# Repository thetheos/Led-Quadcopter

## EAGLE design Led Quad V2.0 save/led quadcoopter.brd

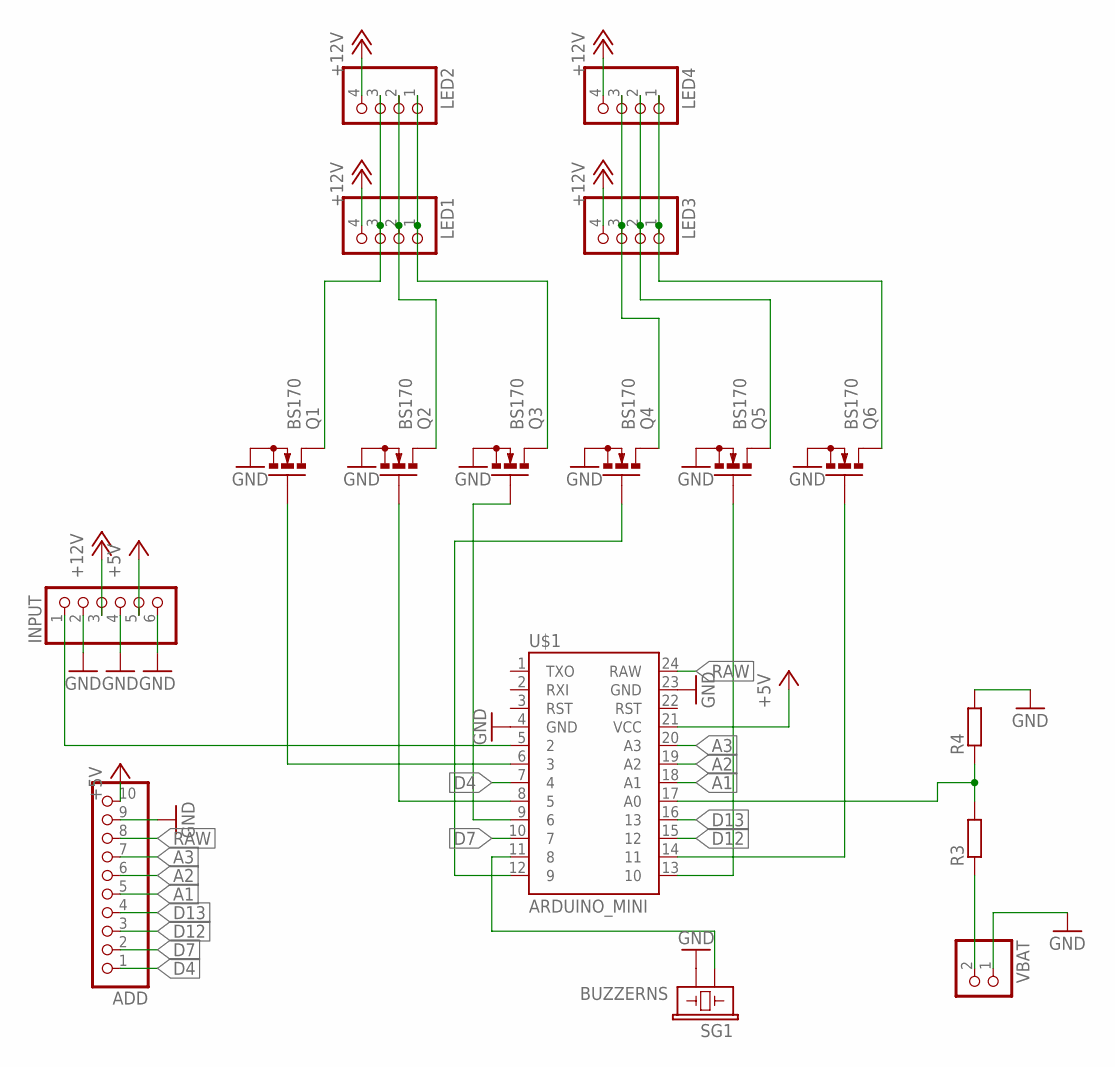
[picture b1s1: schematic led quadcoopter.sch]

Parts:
ADD: PINHD-1X10; 1X10
INPUT: PINHD-1X6; 1X06
LED1, LED2, LED3, LED4: PINHD-1X4; 1X04
Q1, Q2, Q3, Q4, Q5, Q6: BS170; SOT54E
R3, R4: R-EU_0207/10; 0207/10
SG1: BUZZERNS; BUZZER-12MM-NS
U$1: ARDUINO_MINI
VBAT: PINHD-1X2; 1X02

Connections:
+5V: ADD.10, INPUT.5, U$1.21 (VCC)
+12V: INPUT.3, LED1.4, LED2.4, LED3.4, LED4.4
A1: ADD.5, U$1.18 (A1)
A2: ADD.6, U$1.19 (A2)
A3: ADD.7, U$1.20 (A3)
D4: ADD.1, U$1.7 (4)
D7: ADD.2, U$1.10 (7)
D12: ADD.3, U$1.15 (12)
D13: ADD.4, U$1.16 (13)
GND: ADD.9, INPUT.2, INPUT.4, INPUT.6, Q1.S, Q2.S, Q3.S, Q4.S, Q5.S, Q6.S, R4.2, SG1.- (2), U$1.4 (GND), U$1.23 (GND), VBAT.1
unnamed: LED1.3, LED2.3, Q1.D
unnamed: LED1.2, LED2.2, Q2.D
unnamed: SG1.+ (1), U$1.11 (8)
unnamed: INPUT.1, U$1.5 (2)
unnamed: LED1.1, LED2.1, Q3.D
unnamed: LED3.3, LED4.3, Q4.D
unnamed: LED3.2, LED4.2, Q5.D
unnamed: LED3.1, LED4.1, Q6.D
unnamed: Q1.G, U$1.6 (3)
unnamed: Q2.G, U$1.8 (5)
unnamed: Q3.G, U$1.9 (6)
unnamed: Q4.G, U$1.12 (9)
unnamed: Q5.G, U$1.13 (10)
unnamed: Q6.G, U$1.14 (11)
unnamed: R3.1, VBAT.2
unnamed: R3.2, R4.1, U$1.17 (A0)
RAW: ADD.8, U$1.24 (RAW)

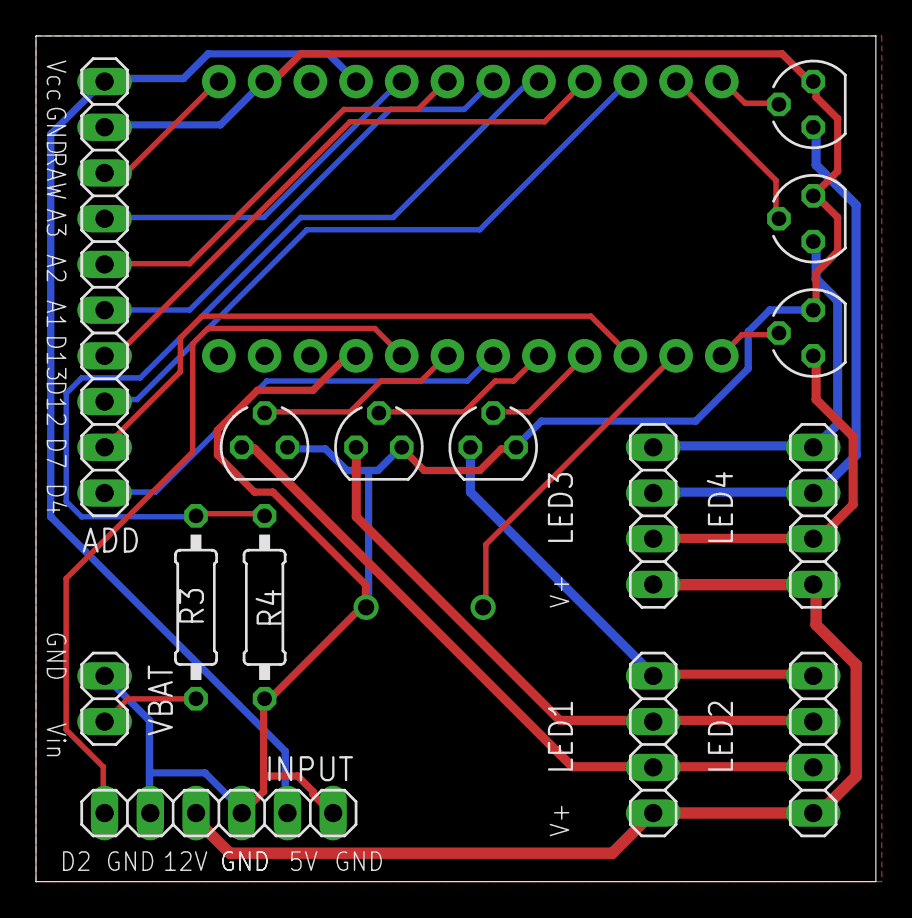
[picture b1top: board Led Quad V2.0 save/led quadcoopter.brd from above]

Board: 2 copper layers, 46.7 x 47.0 mm, 17 parts (1 on the bottom side), 27 nets.

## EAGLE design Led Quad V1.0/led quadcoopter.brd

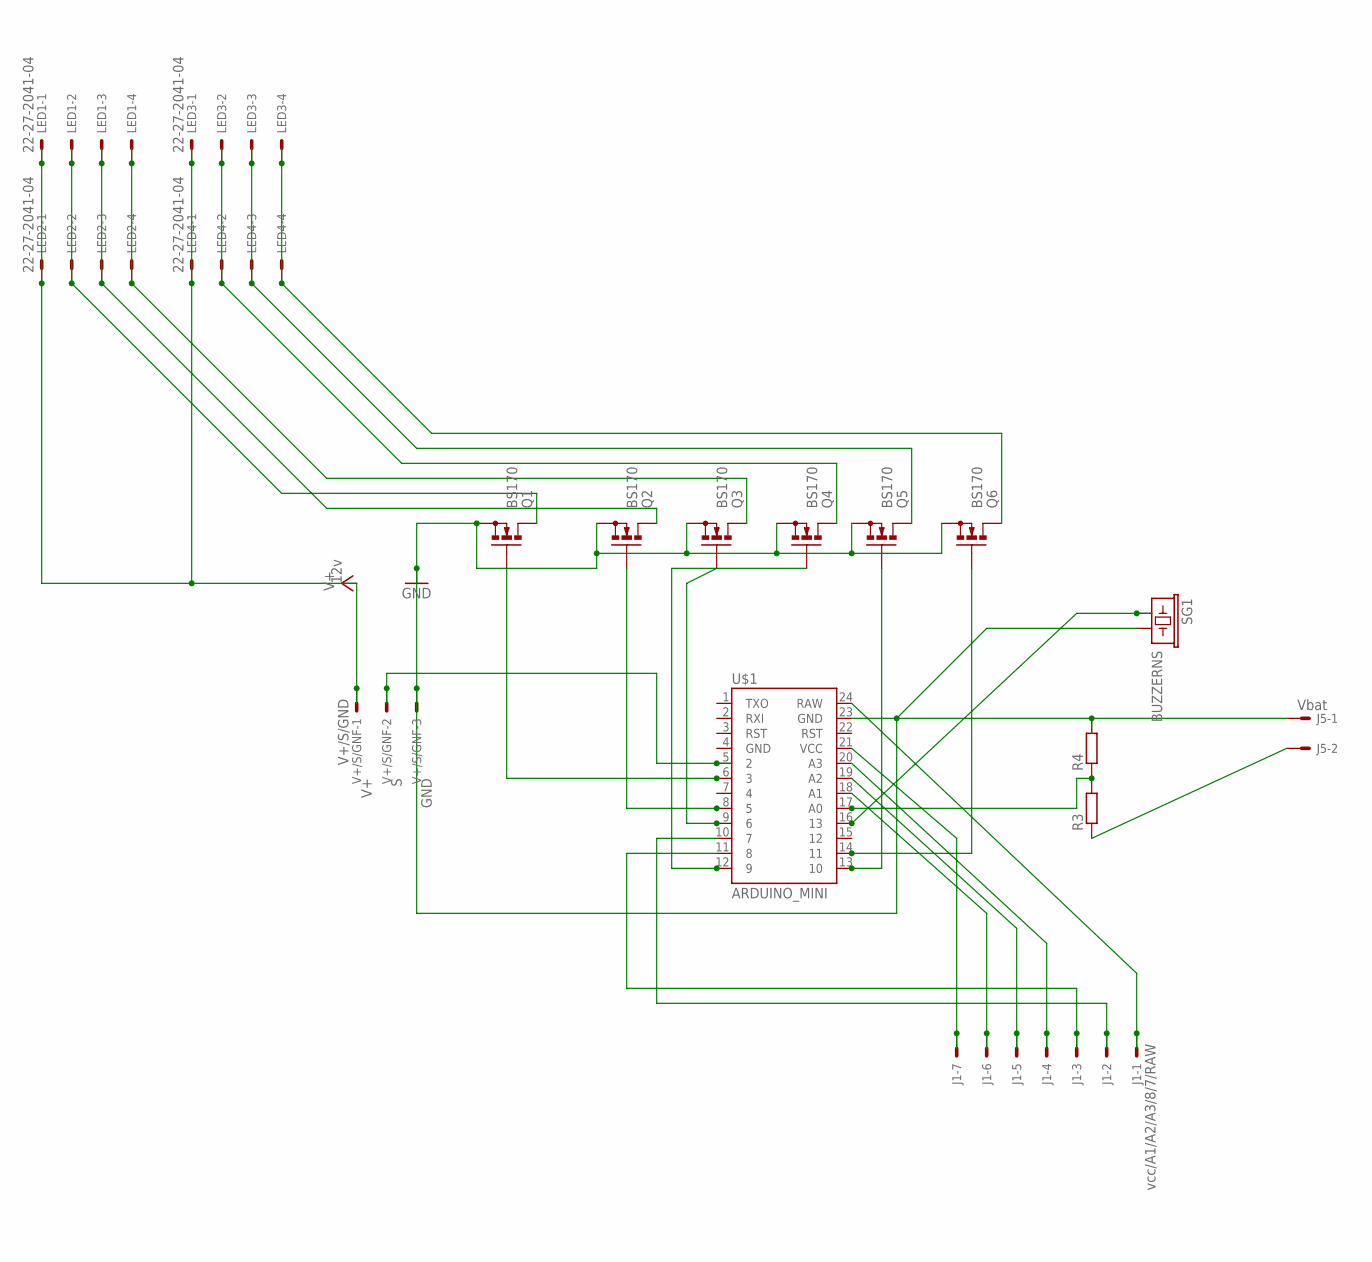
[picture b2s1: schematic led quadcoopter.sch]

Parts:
J1: vcc/A1/A2/A3/8/7/RAW; 6410-07
J5: Vbat; 6410-02
LED1, LED2, LED3, LED4: 22-27-2041-04; 6410-04
Q1, Q2, Q3, Q4, Q5, Q6: BS170; SOT54E
R3, R4: R-EU_0207/10; 0207/10
SG1: BUZZERNS; BUZZER-12MM-NS
U$1: ARDUINO_MINI
V+/S/GNF: V+/S/GND; 6410-03

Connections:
GND: J5.1, Q1.S, Q2.S, Q3.S, Q4.S, Q5.S, Q6.S, R4.2, SG1.- (2), U$1.23 (GND), V+/S/GNF.3
unnamed: LED1.4, LED2.4, Q3.D
unnamed: R3.2, R4.1, U$1.17 (A0)
unnamed: SG1.+ (1), U$1.16 (13)
unnamed: J1.1, U$1.24 (RAW)
unnamed: J1.7, U$1.21 (VCC)
unnamed: J1.6, U$1.18 (A1)
unnamed: J1.5, U$1.19 (A2)
unnamed: LED1.2, LED2.2, Q1.D
unnamed: LED1.3, LED2.3, Q2.D
unnamed: LED3.2, LED4.2, Q4.D
unnamed: LED3.3, LED4.3, Q5.D
unnamed: LED3.4, LED4.4, Q6.D
unnamed: U$1.5 (2), V+/S/GNF.2
unnamed: J1.4, U$1.20 (A3)
unnamed: J1.3, U$1.11 (8)
unnamed: Q1.G, U$1.6 (3)
unnamed: Q2.G, U$1.8 (5)
unnamed: Q3.G, U$1.9 (6)
unnamed: Q4.G, U$1.12 (9)
unnamed: Q5.G, U$1.13 (10)
unnamed: Q6.G, U$1.14 (11)
unnamed: J1.2, U$1.10 (7)
V+: LED1.1, LED2.1, LED3.1, LED4.1, V+/S/GNF.1
VBAT: J5.2, R3.1

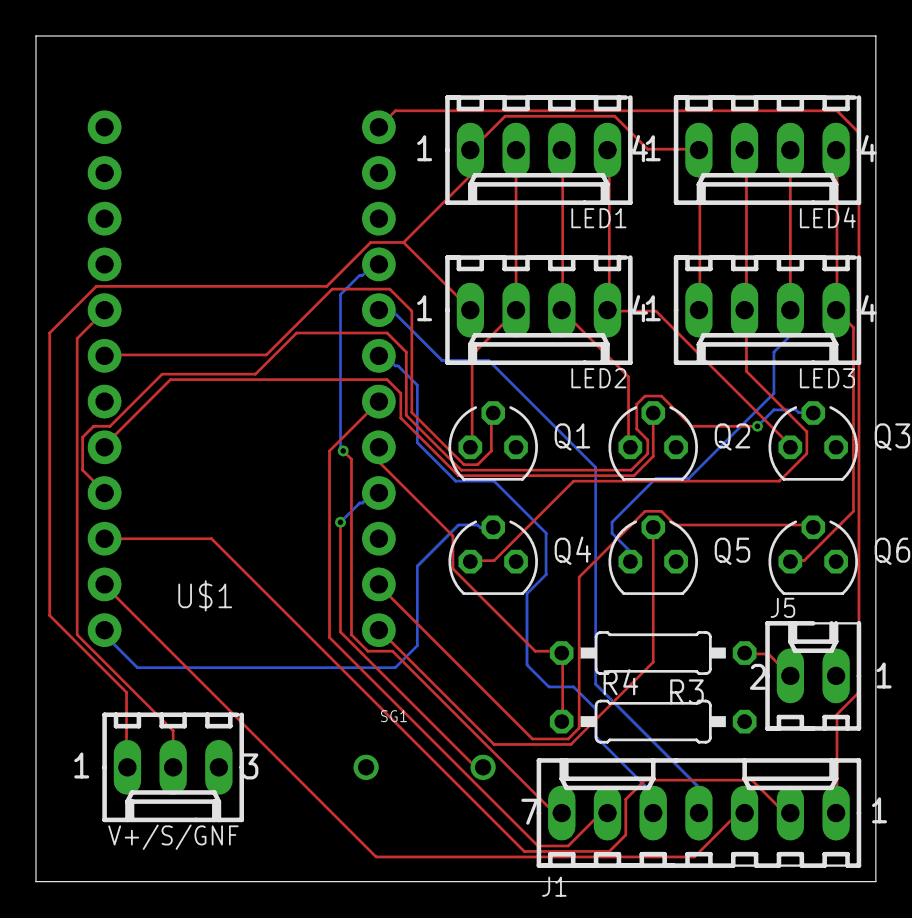
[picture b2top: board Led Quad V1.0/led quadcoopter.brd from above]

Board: 2 copper layers, 46.7 x 47.0 mm, 17 parts (0 on the bottom side), 25 nets.

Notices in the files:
parts and their libraries:
SparkFun-Electromechanical: Licensing: Creative Commons ShareAlike 4.0 International - https://creativecommons.org/licenses/by-sa/4.0
